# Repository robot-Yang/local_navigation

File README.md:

# local_navigation
# This project is for RealSense D435 camera in UP Square
# "install" directionary includes the OS installation, software configuration and some other settings.
# "catkin_ws" is a ROS folder, all the codes will be compiled here.

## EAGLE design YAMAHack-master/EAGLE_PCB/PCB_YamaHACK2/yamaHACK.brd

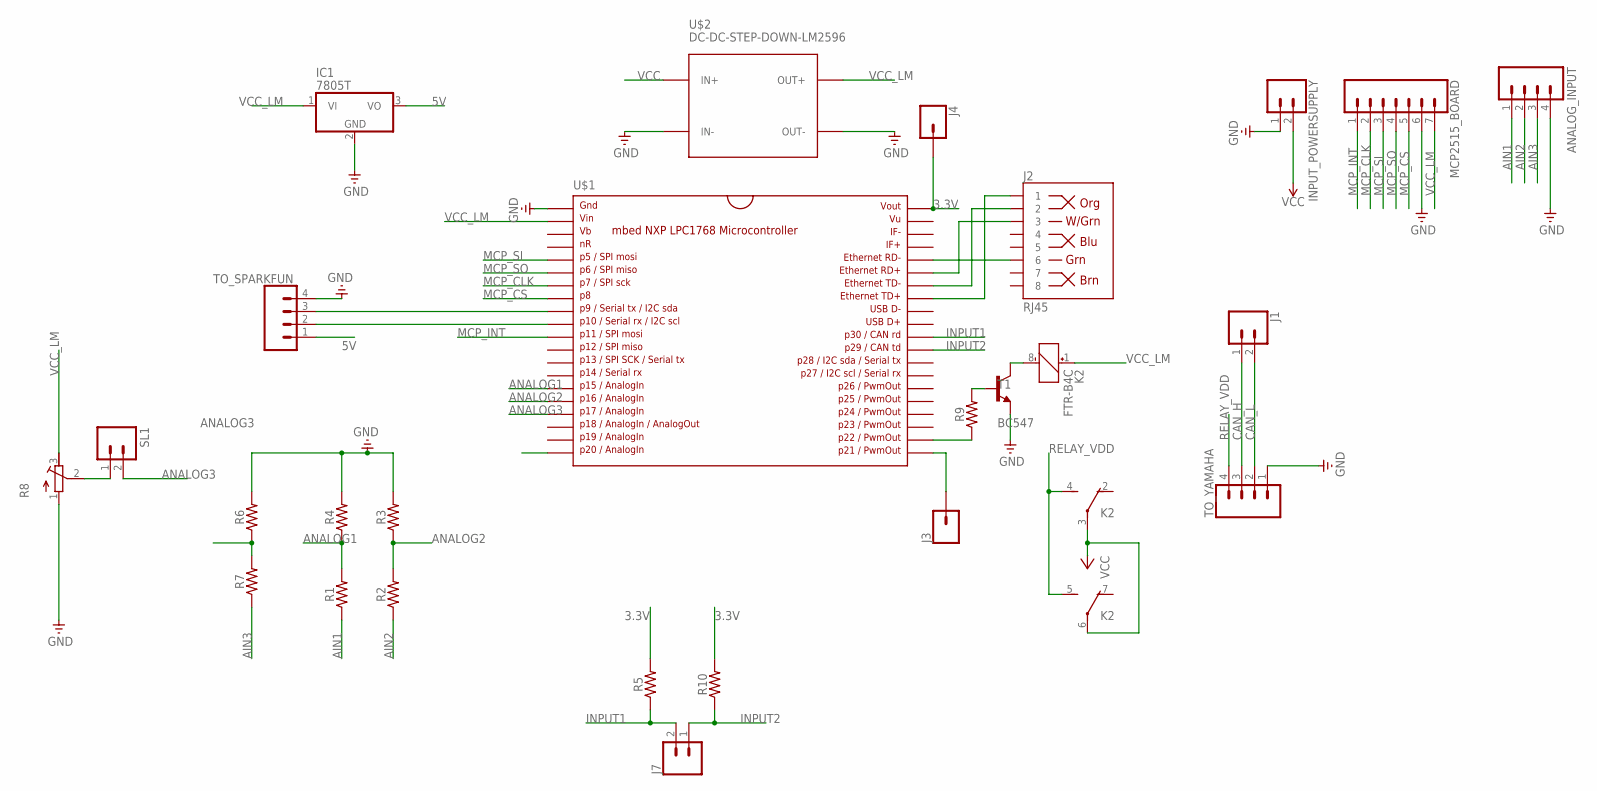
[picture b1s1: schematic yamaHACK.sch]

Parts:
ANALOG_INPUT: M04; 04P
IC1: 7805T; TO220H
INPUT_POWERSUPPLY: CONN_02PTH3; 1X02_LONGPADS
J1, J7: CONN_02; 1X02
J2: RJ45; RJ45-8
J3, J4: CONN_01OFFSET; 1X01_OFFSET
K2: FTR-B4C
MCP2515_BOARD: CONN_07LONGPADS; 1X07_LONGPADS
R1, R2, R3, R4, R5, R6, R7, R9, R10: AXIAL-0.3
R8: R-TRIMM3296W; RTRIM3296W
SL1: M02; 02P
T1: BC547; TO92
TO_SPARKFUN: CONN_04; 1X04
TO_YAMAHA: CONN_04; 1X04
U$1: MBED1768; DIL40_0.9
U$2: DC-DC-STEP-DOWN-LM2596

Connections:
3.3V: J4.1, R5.P$2 (2), R10.P$2 (2), U$1.40
5V: IC1.3 (VO), TO_SPARKFUN.1
AIN1: ANALOG_INPUT.1, R1.P$1 (1)
AIN2: ANALOG_INPUT.2, R2.P$1 (1)
AIN3: ANALOG_INPUT.3, R7.P$1 (1)
ANALOG1: R1.P$2 (2), R4.P$1 (1), U$1.15
ANALOG2: R2.P$2 (2), R3.P$1 (1), U$1.16
ANALOG3: R6.P$1 (1), R7.P$2 (2), SL1.2, U$1.17
CAN_H: J1.1, TO_YAMAHA.3
CAN_L: J1.2, TO_YAMAHA.2
GND: ANALOG_INPUT.4, IC1.2 (GND), INPUT_POWERSUPPLY.1, MCP2515_BOARD.6, R3.P$2 (2), R4.P$2 (2), R6.P$2 (2), R8.1 (A), T1.1 (E), TO_SPARKFUN.4, TO_YAMAHA.1, U$1.1, U$2.IN-, U$2.OUT-
INPUT1: J7.2, R5.P$1 (1), U$1.30
INPUT2: J7.1, R10.P$1 (1), U$1.29
MCP_CLK: MCP2515_BOARD.2, U$1.7
MCP_CS: MCP2515_BOARD.5, U$1.8
MCP_INT: MCP2515_BOARD.1, U$1.11
MCP_SI: MCP2515_BOARD.3, U$1.5
MCP_SO: MCP2515_BOARD.4, U$1.6
unnamed: J3.1, U$1.21
unnamed: R8.2 (S), SL1.1
unnamed: K2.8 (-), T1.3 (C)
unnamed: R9.P$1 (1), U$1.22
unnamed: R9.P$2 (2), T1.2 (B)
unnamed: J2.1, U$1.33
unnamed: J2.2, U$1.34
unnamed: J2.3, U$1.35
unnamed: J2.6, U$1.36
unnamed: TO_SPARKFUN.2, U$1.10
unnamed: TO_SPARKFUN.3, U$1.9
RELAY_VDD: K2.4 (S), K2.5 (S), TO_YAMAHA.4
VCC: INPUT_POWERSUPPLY.2, K2.3, K2.6, U$2.IN+
VCC_LM: IC1.1 (VI), K2.1 (+), MCP2515_BOARD.7, R8.3 (E), U$1.2, U$2.OUT+

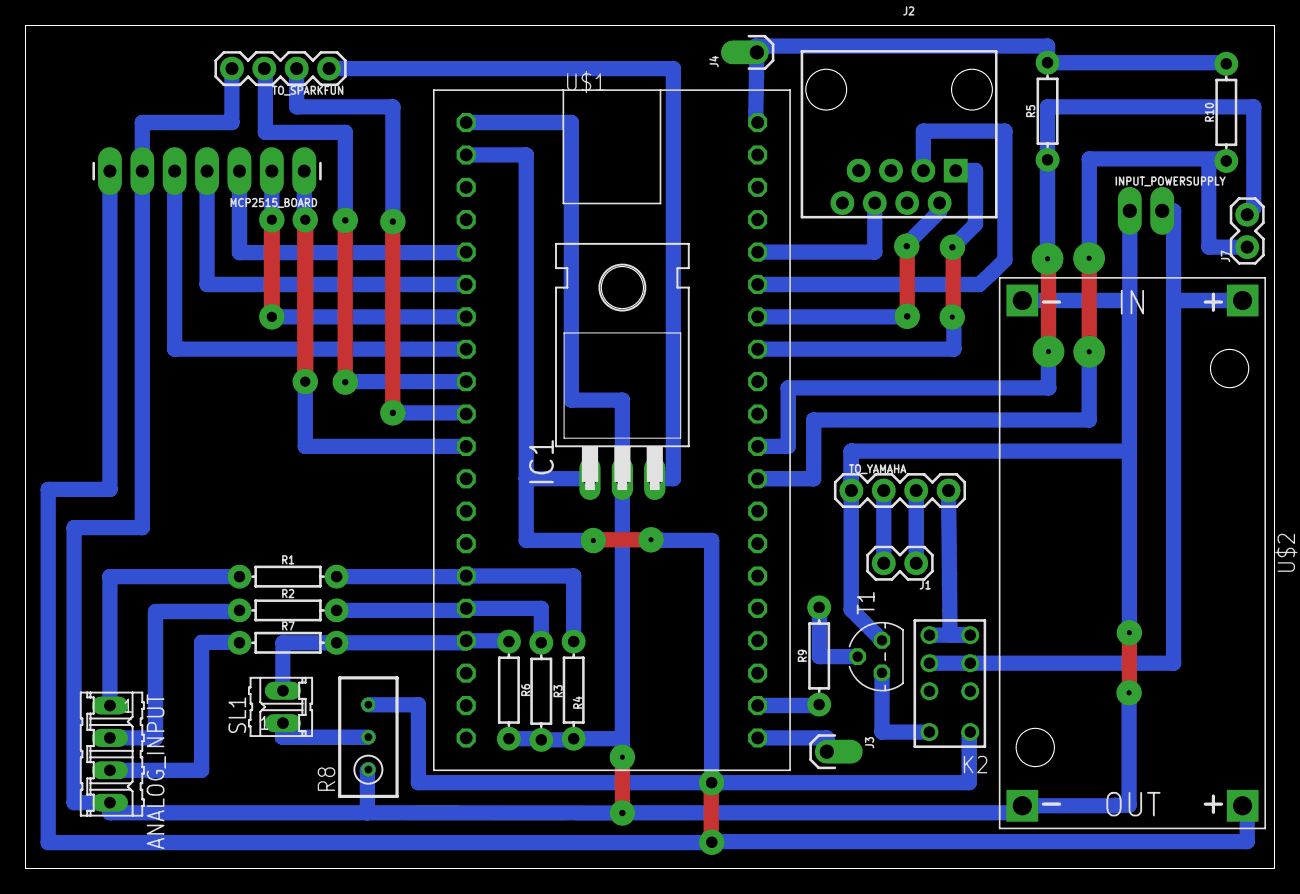
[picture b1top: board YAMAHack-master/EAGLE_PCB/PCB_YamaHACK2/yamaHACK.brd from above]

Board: 2 copper layers, 98.0 x 66.1 mm, 26 parts (0 on the bottom side), 32 nets.

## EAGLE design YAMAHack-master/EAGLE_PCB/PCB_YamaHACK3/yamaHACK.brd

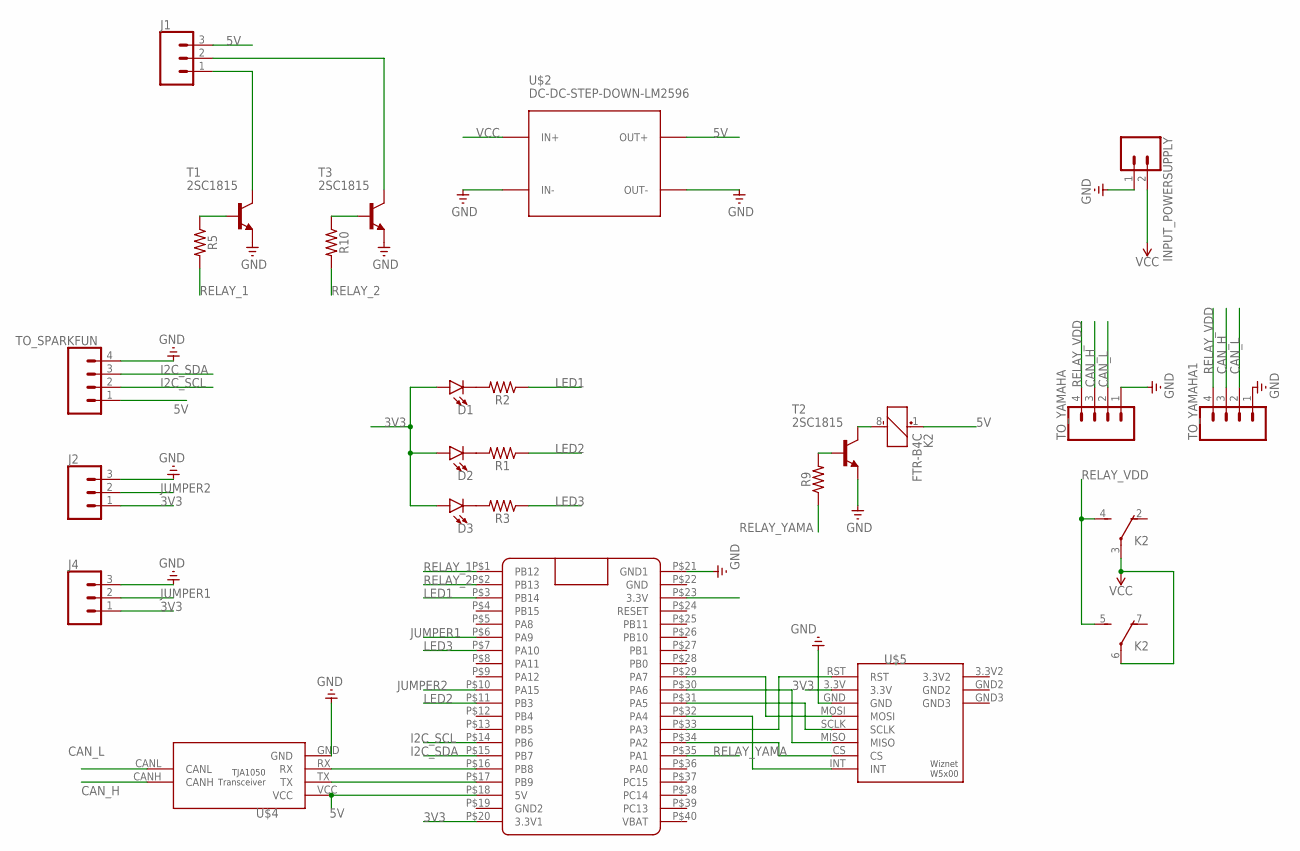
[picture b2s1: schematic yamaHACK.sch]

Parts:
D1, D2, D3: LED3MM; LED_3MM
INPUT_POWERSUPPLY: CONN_02PTH3; 1X02_LONGPADS
J1, J2, J4: CONN_03; 1X03
K2: FTR-B4C
R1, R2, R3, R5, R9, R10: AXIAL-0.3
T1, T2, T3: 2SC1815; TO92-ECB
TO_SPARKFUN: CONN_04; 1X04
TO_YAMAHA, TO_YAMAHA1: CONN_04; 1X04
U$2: DC-DC-STEP-DOWN-LM2596
U$3: BLUE_PILL
U$4: TJA1050TJA1050_WH; TJA1050_WH
U$5: WIZNET; WIZNET_LITE

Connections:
3V3: D1.A, D2.A, D3.A, J2.1, J4.1, U$3.P$20 (3.3V1), U$3.P$23 (3.3V), U$5.3.3V
5V: J1.3, K2.1 (+), TO_SPARKFUN.1, U$2.OUT+, U$3.P$18 (5V), U$4.VCC
CAN_H: TO_YAMAHA.3, TO_YAMAHA1.3, U$4.CANH
CAN_L: TO_YAMAHA.2, TO_YAMAHA1.2, U$4.CANL
GND: INPUT_POWERSUPPLY.1, J2.3, J4.3, T1.E, T2.E, T3.E, TO_SPARKFUN.4, TO_YAMAHA.1, TO_YAMAHA1.1, U$2.IN-, U$2.OUT-, U$3.P$21 (GND1), U$4.GND, U$5.GND
I2C_SCL: TO_SPARKFUN.2, U$3.P$14 (PB6)
I2C_SDA: TO_SPARKFUN.3, U$3.P$15 (PB7)
JUMPER1: J4.2, U$3.P$6 (PA9)
JUMPER2: J2.2, U$3.P$10 (PA15)
LED1: R2.P$1 (1), U$3.P$3 (PB14)
LED2: R1.P$1 (1), U$3.P$11 (PB3)
LED3: R3.P$1 (1), U$3.P$7 (PA10)
unnamed: U$3.P$34 (PA2), U$5.CS
unnamed: U$3.P$16 (PB8), U$4.RX
unnamed: U$3.P$33 (PA3), U$5.RST
unnamed: U$3.P$32 (PA4), U$5.INT
unnamed: K2.8 (-), T2.C
unnamed: U$3.P$31 (PA5), U$5.SCLK
unnamed: R9.P$2 (2), T2.B
unnamed: U$3.P$17 (PB9), U$4.TX
unnamed: U$3.P$30 (PA6), U$5.MISO
unnamed: U$3.P$29 (PA7), U$5.MOSI
unnamed: D2.K (C), R1.P$2 (2)
unnamed: R5.P$1 (1), T1.B
unnamed: D1.K (C), R2.P$2 (2)
unnamed: J1.1, T1.C
unnamed: R10.P$1 (1), T3.B
unnamed: J1.2, T3.C
unnamed: D3.K (C), R3.P$2 (2)
RELAY_1: R5.P$2 (2), U$3.P$1 (PB12)
RELAY_2: R10.P$2 (2), U$3.P$2 (PB13)
RELAY_VDD: K2.4 (S), K2.5 (S), TO_YAMAHA.4, TO_YAMAHA1.4
RELAY_YAMA: R9.P$1 (1), U$3.P$35 (PA1)
VCC: INPUT_POWERSUPPLY.2, K2.3, K2.6, U$2.IN+

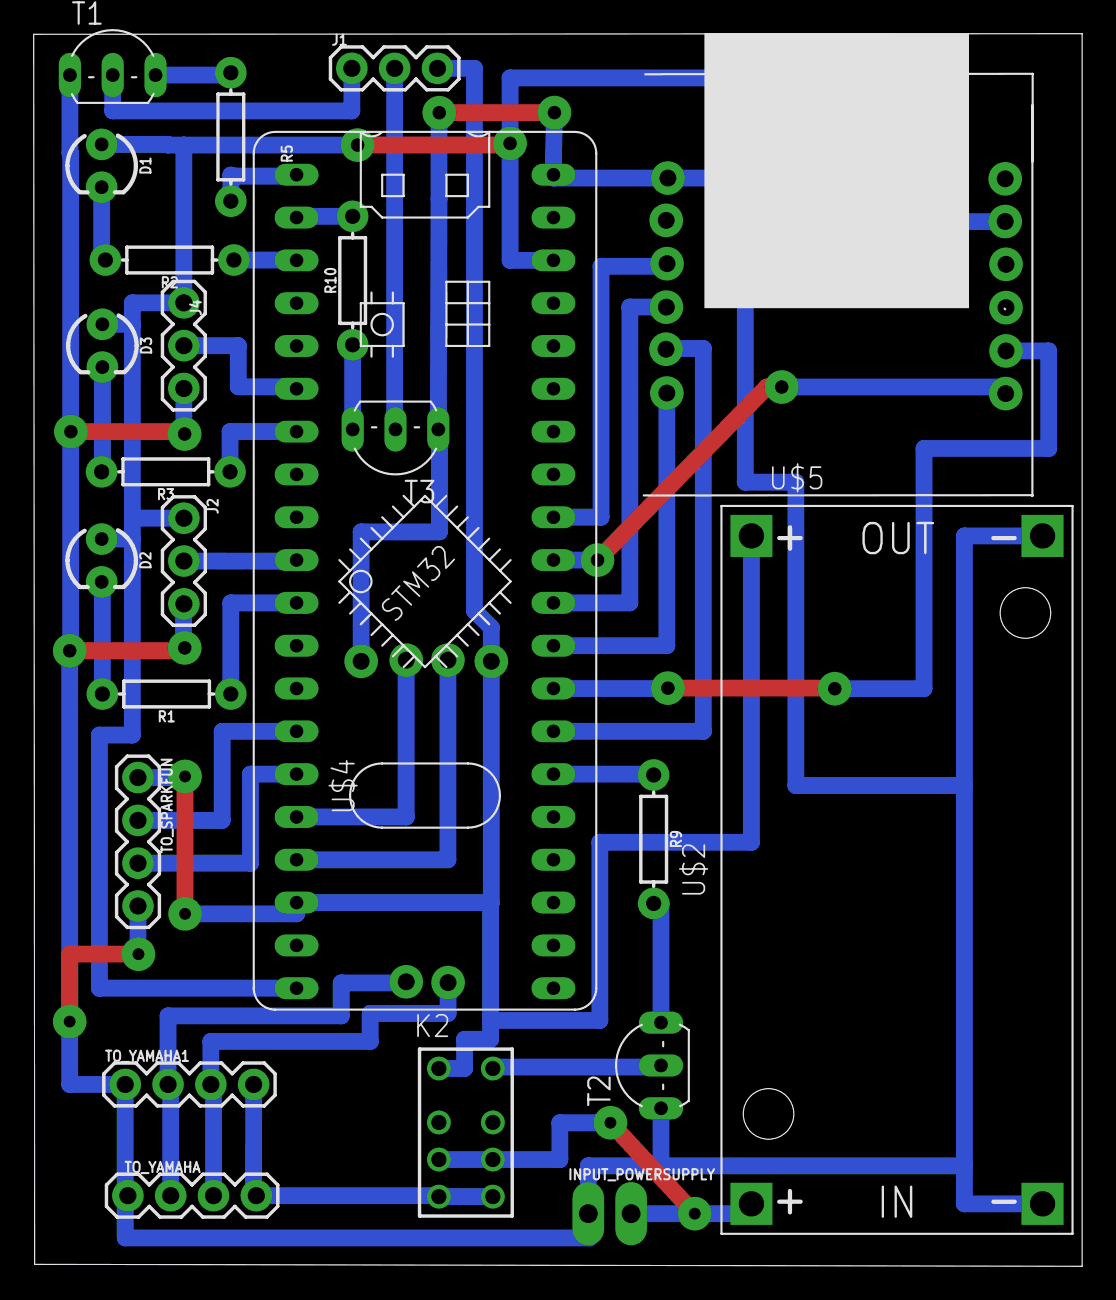
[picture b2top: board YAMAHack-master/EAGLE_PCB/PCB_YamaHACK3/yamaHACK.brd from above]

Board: 2 copper layers, 62.2 x 73.1 mm, 24 parts (0 on the bottom side), 34 nets.

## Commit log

2019-02-14 Create up2_change
2019-02-14 Create pcl_install
2019-02-14 Update pcl_install
    No rule to make target error
2019-02-17 Create realsense_install
2019-02-17 Rename realsense_install to realsense_install.sh
2019-02-17 Rename up2_change to up2_change.sh
2019-02-17 Rename pcl_install to pcl_install.sh
2019-02-17 Create rs_pcl1
2019-02-18 Rename intel_ros_install.sh to intelRos_install.sh
2019-03-29 rearrangement
2019-04-03 rewrite readme
2019-05-26 ADDA modify
2019-05-26 python code added
2019-06-05 add explanation for missing packages
2019-06-08 motion planing added
2019-06-20 path planning5 update
2019-09-03 a lot change
2019-09-26 ADDA library two borad update
2019-10-12 simulation added
2019-11-05 summary work in LASA
2020-01-09 after change username
2020-05-09 Update README.md
    updated instructions
2020-06-14 add new simulation code
2020-06-14 revert README.md
2021-01-06 update until T-mech submission

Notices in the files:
parts and their libraries:
SparkFun-Boards: Licensing: Creative Commons ShareAlike 4.0 International - https://creativecommons.org/licenses/by-sa/4.0
supply0: Copyright (C) 2007, Bob Starr
diy-modules: Released under the Creative Commons Attribution 4.0 International License: http://creativecommons.org/licenses/by/4.0
